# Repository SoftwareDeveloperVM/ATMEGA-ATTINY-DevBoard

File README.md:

# ATMEGA-ATTINY-DevBoard

The purpose of this Fusion DevBoard is to control a set of Seven-Segment displays, with the ATTINY focusing on it's own section. With a header pinout to the majority of each microcontroller's pins, it allows the DevBoard user to load custom on it to build flexible systems.

The ATMEGA328P Chip is connected to a reset button with a 10K ohm resistor, (2x) 22 pf Ceramic Capacitors, a 10 uF polarized capacitor, and a 16 mHZ crystal oscillator for the clock signal. This forms a basic circuit, which is attached to a ATTINY85 chip used to control the (4x) Seven-Segment Display, allowing the user to control that through custom code.

### Circuit Schematic

### PCB Design Layout

### 3D Model Visualization

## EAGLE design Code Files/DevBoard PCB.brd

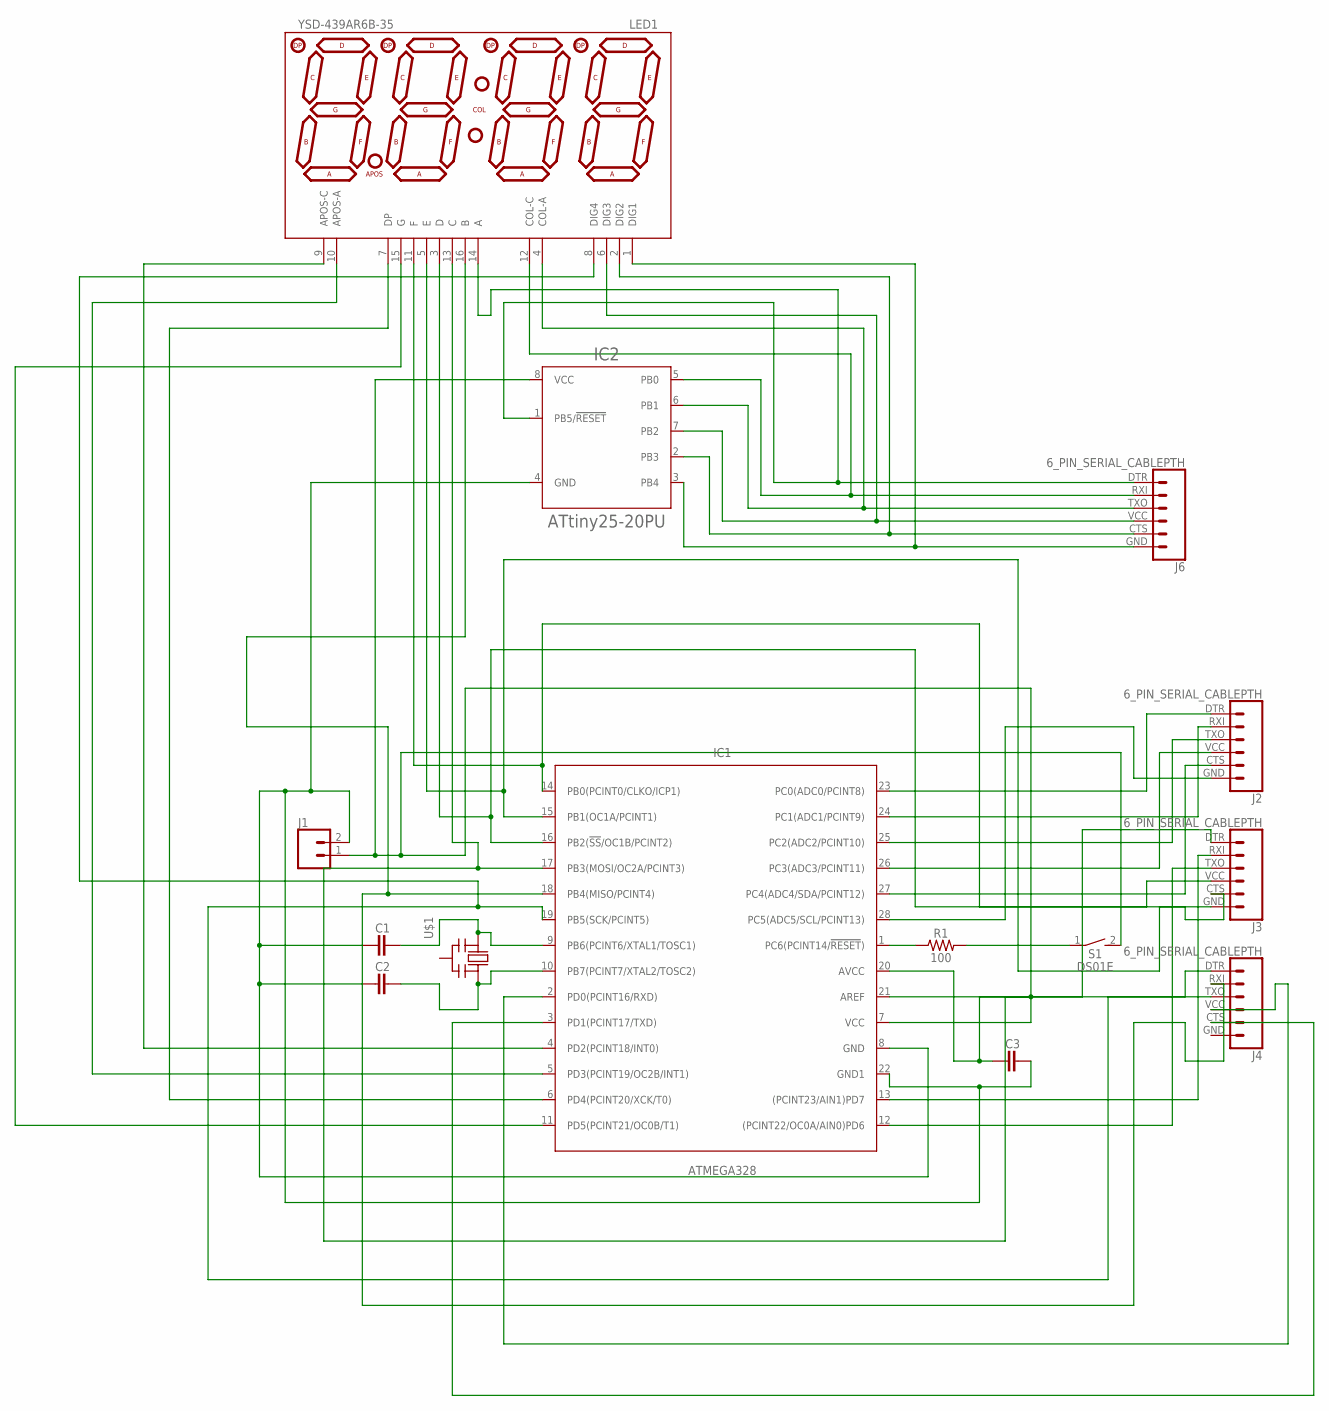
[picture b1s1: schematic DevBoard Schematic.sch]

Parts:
C1, C2, C3: CAPACITORCERAMIC-2.54MM; CAP-THRU-2.54MM
IC1: ATMEGA328; DIP1016W53P254L3467H457Q28B
IC2: ATtiny25-20PU; DIP787W55P254L958H533Q8B-8P3
J1: CONN_02; 1X02
J2, J3, J4, J6: 6_PIN_SERIAL_CABLEPTH; FTDI_BASIC
LED1: YSD-439AR6B-35; 7-SEGMENT-4DIGIT-YOUNGSUN
R1: 100; AXIAL-0.3
S1: DS01E; DS-01
U$1: CERMOSCILL-THM; CERM_OSC

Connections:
unnamed: C1.1, IC1.9 (PB6(PCINT6/XTAL1/TOSC1)), U$1.P$1 (IN)
unnamed: C2.1, IC1.10 (PB7(PCINT7/XTAL2/TOSC2)), U$1.P$3 (OUT)
unnamed: IC1.23 (PC0(ADC0/PCINT8)), J2.DTR (1)
unnamed: C3.2, IC1.7 (VCC), IC1.20 (AVCC), IC2.8 (VCC), J1.1, S1.2
unnamed: IC1.1 (PC6(PCINT14/!RESET!)), R1.P$1 (1)
unnamed: R1.P$2 (2), S1.1
unnamed: IC1.24 (PC1(ADC1/PCINT9)), J2.RXI (2)
unnamed: C1.2, C2.2, C3.1, IC1.8 (GND), IC1.22 (GND1), IC2.4 (GND), J1.2
unnamed: IC1.25 (PC2(ADC2/PCINT10)), J2.TXO (3)
unnamed: IC1.26 (PC3(ADC3/PCINT11)), J2.VCC (4)
unnamed: IC1.27 (PC4(ADC4/SDA/PCINT12)), J2.CTS (5)
unnamed: IC1.28 (PC5(ADC5/SCL/PCINT13)), J2.GND (6)
unnamed: IC1.21 (AREF), J3.DTR (1)
unnamed: IC1.13 ((PCINT23/AIN1)PD7), J3.RXI (2)
unnamed: IC1.12 ((PCINT22/OC0A/AIN0)PD6), J3.TXO (3)
unnamed: IC1.14 (PB0(PCINT0/CLKO/ICP1)), J3.VCC (4), LED1.11 (F)
unnamed: IC1.15 (PB1(OC1A/PCINT1)), J3.CTS (5), LED1.5 (E)
unnamed: IC1.16 (PB2(!SS!/OC1B/PCINT2)), J3.GND (6), LED1.3 (D)
unnamed: IC1.17 (PB3(MOSI/OC2A/PCINT3)), J4.DTR (1), LED1.13 (C)
unnamed: IC1.18 (PB4(MISO/PCINT4)), J4.RXI (2), LED1.16 (B)
unnamed: IC1.19 (PB5(SCK/PCINT5)), J4.TXO (3), LED1.8 (DIG4)
unnamed: IC1.2 (PD0(PCINT16/RXD)), J4.VCC (4)
unnamed: IC1.3 (PD1(PCINT17/TXD)), J4.CTS (5)
unnamed: IC2.3 (PB4), J6.GND (6), LED1.1 (DIG1)
unnamed: IC2.2 (PB3), J6.CTS (5), LED1.2 (DIG2)
unnamed: IC2.7 (PB2), J6.VCC (4), LED1.6 (DIG3)
unnamed: IC2.6 (PB1), J6.TXO (3), LED1.4 (COL-A)
unnamed: IC2.5 (PB0), J6.RXI (2), LED1.12 (COL-C)
unnamed: IC2.1 (PB5/!RESET!), J6.DTR (1), LED1.14 (A)
unnamed: IC1.4 (PD2(PCINT18/INT0)), LED1.9 (APOS-C)
unnamed: IC1.5 (PD3(PCINT19/OC2B/INT1)), LED1.10 (APOS-A)
unnamed: IC1.6 (PD4(PCINT20/XCK/T0)), LED1.7 (DP)
unnamed: IC1.11 (PD5(PCINT21/OC0B/T1)), LED1.15 (G)

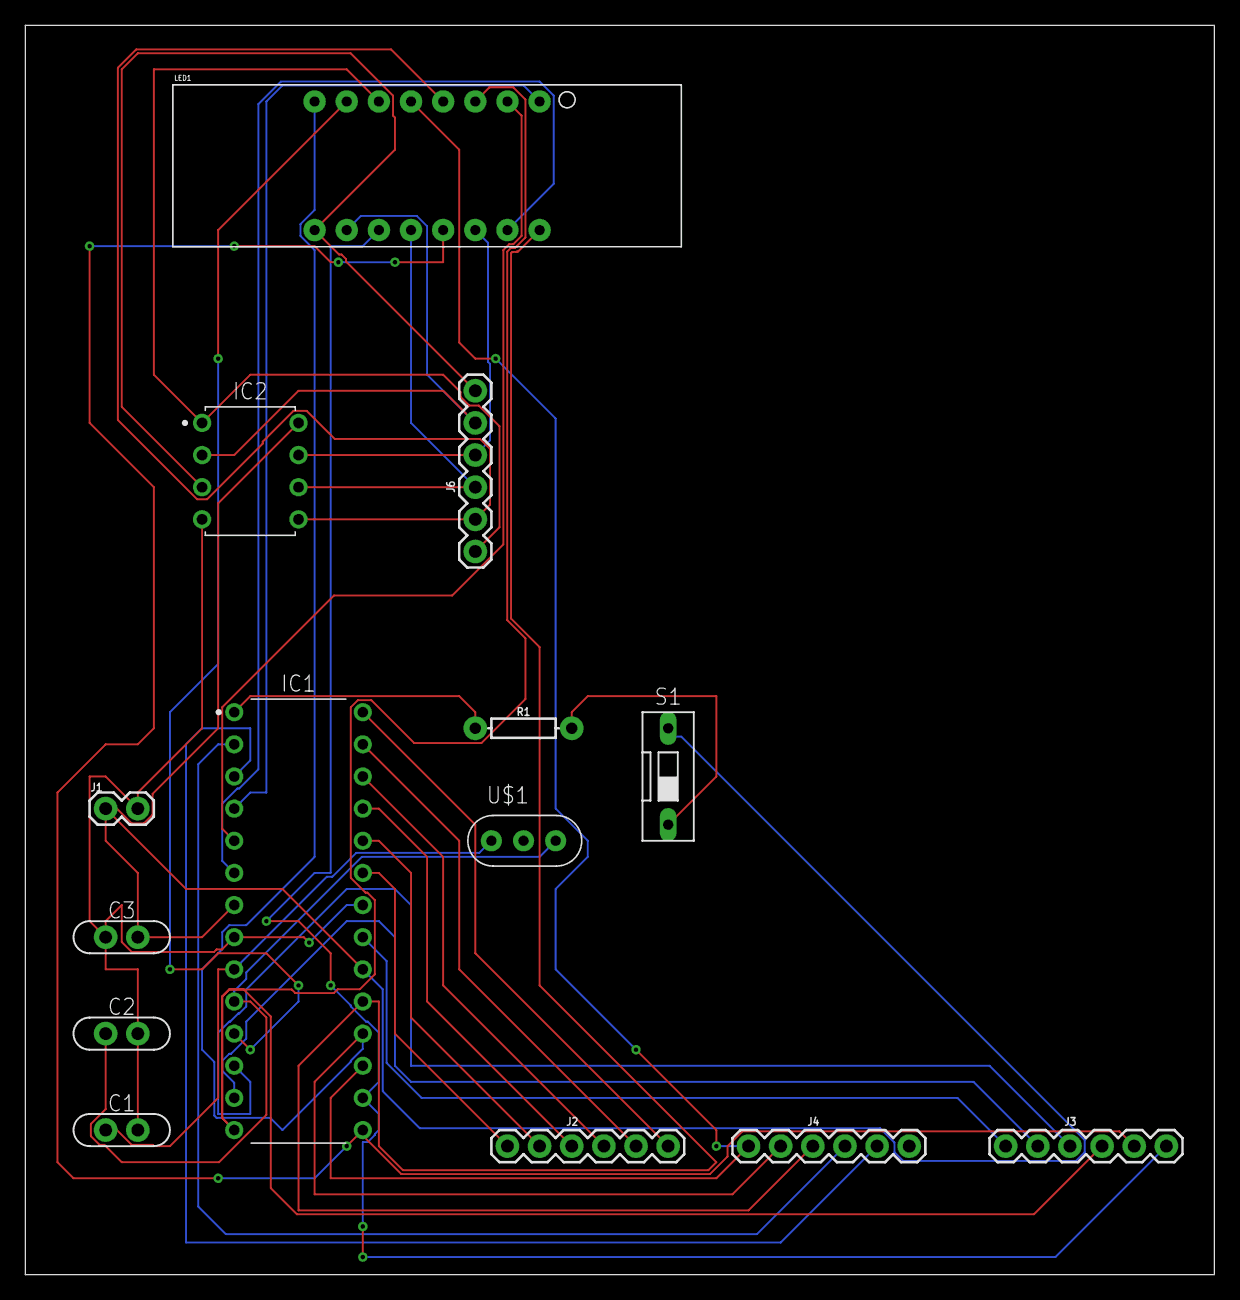
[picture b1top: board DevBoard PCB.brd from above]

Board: 2 copper layers, 94.0 x 98.7 mm, 14 parts (0 on the bottom side), 33 nets.

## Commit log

2025-12-06 Rename Screenshot 2025-12-05 at 8.49.18 PM.png to Schematic.png
2025-12-07 Rename Screenshot 2025-12-07 at 10.30.26 AM.png to PCBDesign.png
2025-12-07 Rename Screenshot 2025-12-07 at 10.31.35 AM.png to 3DModel.png
2025-12-07 Rename Screenshot 2025-12-07 at 10.57.24 AM.png to BOM Screenshot.png
2025-12-07 Rename file.csv to BOM.csv

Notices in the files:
parts and their libraries:
SparkFun-Connectors: Licensing: Creative Commons ShareAlike 4.0 International - https://creativecommons.org/licenses/by-sa/4.0
